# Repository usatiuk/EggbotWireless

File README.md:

# (WIP) EggbotWireless
My attempt at making the ordinary egg-drawing robot a bit special, by ~adding a battery~ and a esp8266 to it.

## Known issues

It's not quite "wireless and portable" yet, for these reasons:

* ~Various battery issues~ (no battery in v2.0!)

* The GCode is generated by inkscape, so you need a computer

## Getting started

### How to build the firmware

Should just work with platformio, but if you're on windows then you need to copy the repo with symlinks 

Also, don't forget to build and upload the LittleFS as well - it contains a simple web interface that allows you to run GCode on the device via Wi-Fi.

If you want to connect to Wi-Fi, then you also should either change the defaults in the ConfigManager.cpp
Or set the configuration via serial:
```
lcp wifiMode client
lcp wifiSSID (your ssid)
lcp wifiPass (your password)
lcw
```
*(lcp stands for "local config put")*

*(lcw stands for "local config write") which saves it to EEPROM*

### How to create GCode

Creating gcode for this thing is quite tricky - you can use the gcodetools Inkscape extension.

The process is supposed to be like this:

1. Open Utils/egg.svg with Inkscape
2. Insert something you want to draw as a child of Layer 1 (the rectangle is the egg boundary)
3. Make it a path
4. Use path to gcode (Also set minimal arc radius in the settings to something big as drawing arcs with g02 is not supported)

You can look at spiral.svg for an example

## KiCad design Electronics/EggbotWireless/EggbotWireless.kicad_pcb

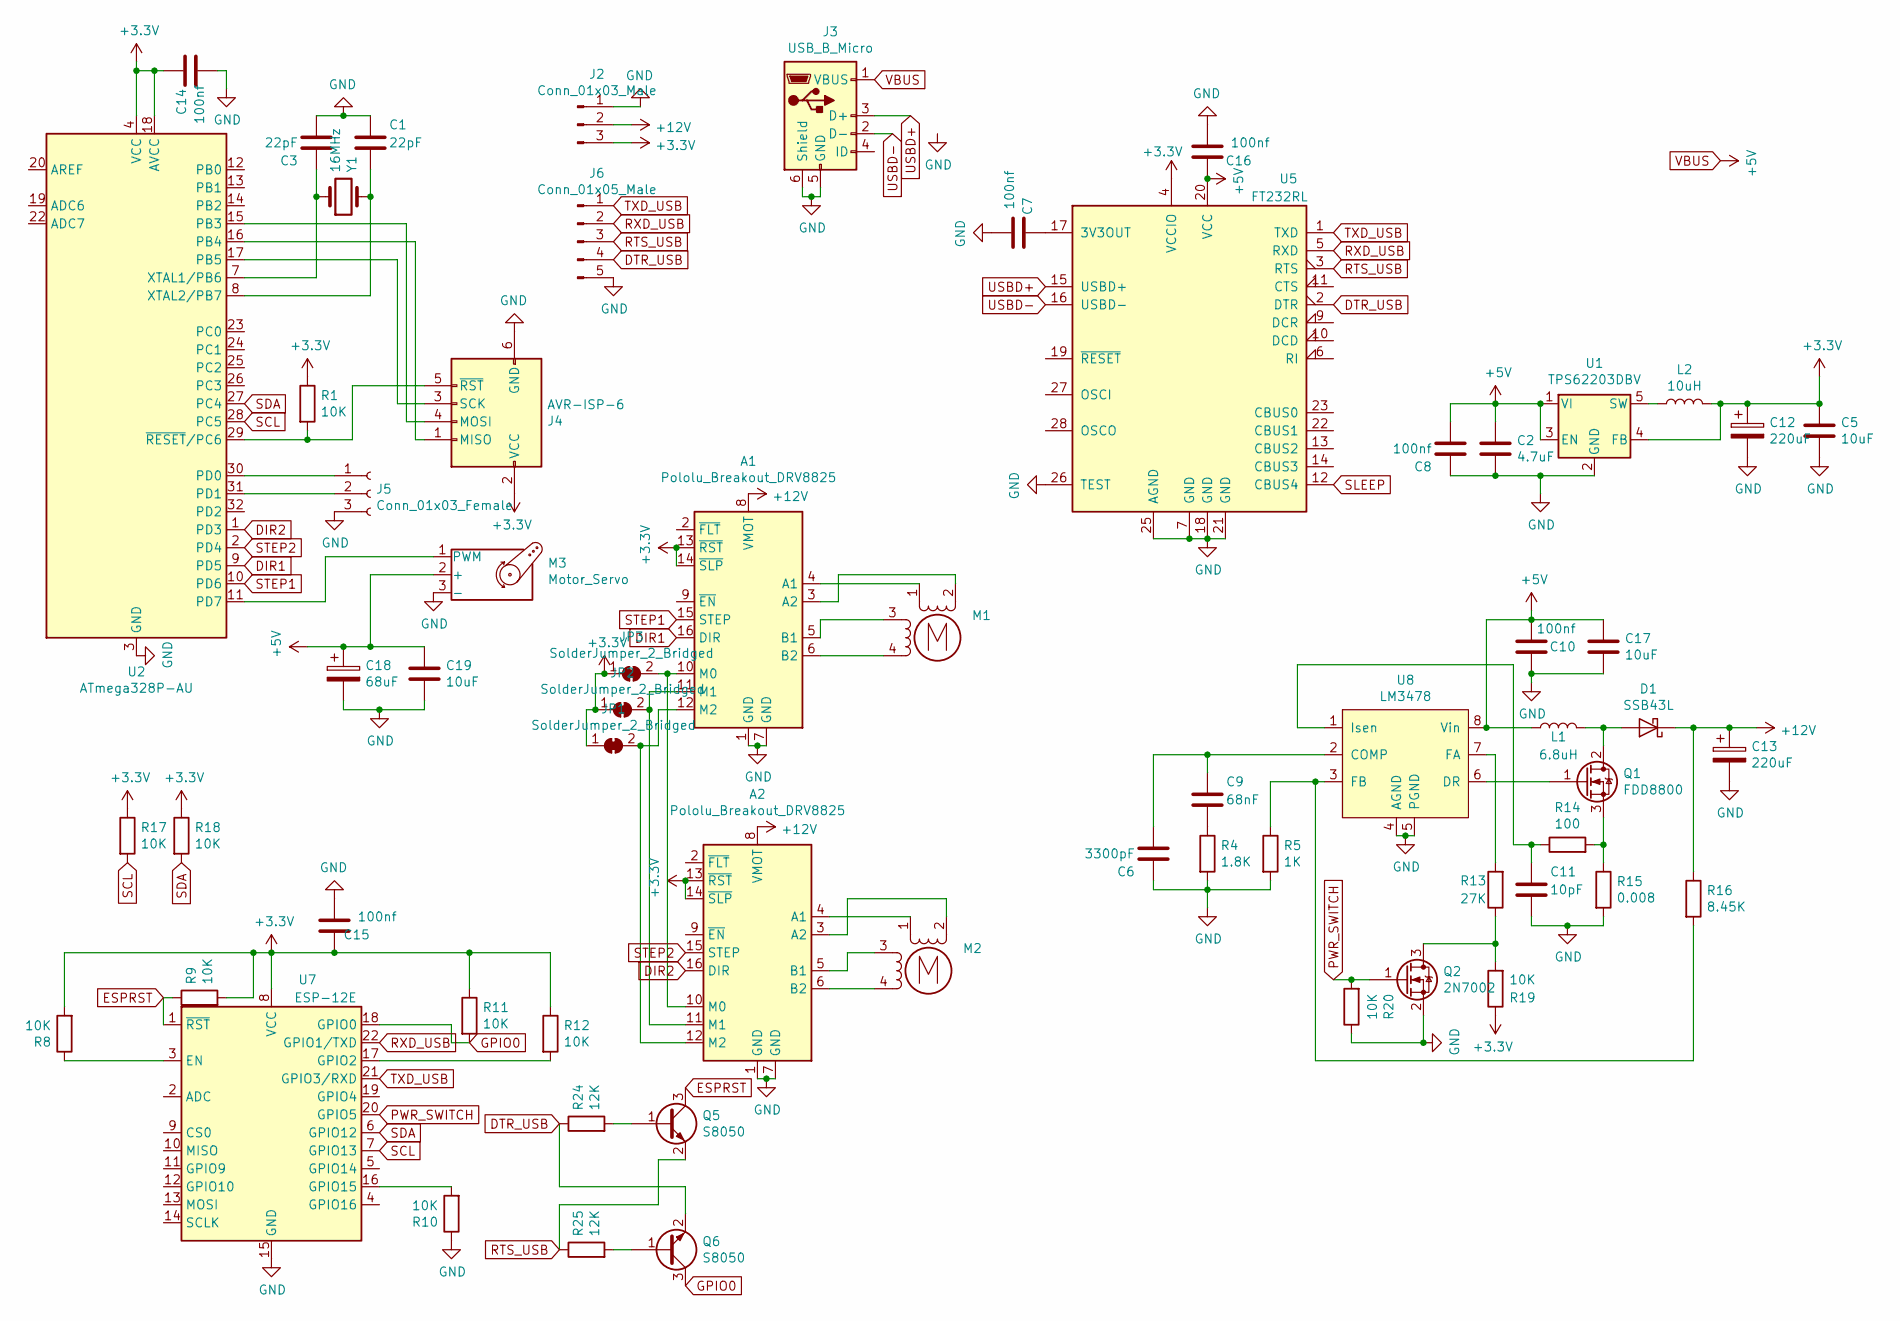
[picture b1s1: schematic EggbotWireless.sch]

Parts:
A1, A2: Pololu_Breakout_DRV8825; Pololu_Breakout-16_15.2x20.3mm
C1, C3: 22pF; C_0805_2012Metric_Pad1.15x1.40mm_HandSolder
C2: 4.7uF; C_0805_2012Metric_Pad1.15x1.40mm_HandSolder
C5, C17: 10uF; C_0805_2012Metric_Pad1.15x1.40mm_HandSolder
C6: 3300pF; C_0805_2012Metric_Pad1.15x1.40mm_HandSolder
C7, C10, C14, C15, C16: 100nf; C_0805_2012Metric_Pad1.15x1.40mm_HandSolder
C8: 100nf; C_0805_2012Metric_Pad1.18x1.45mm_HandSolder
C9: 68nF; C_0805_2012Metric_Pad1.15x1.40mm_HandSolder
C11: 10pF; C_0805_2012Metric_Pad1.15x1.40mm_HandSolder
C12, C13: 220uF; CP_Elec_8x10.5
C18: 68uF; CP_Elec_4x5.8
C19: 10uF; C_0805_2012Metric_Pad1.18x1.45mm_HandSolder
D1: SSB43L; D_SMB_Handsoldering
J2: Conn_01x03_Male; PinHeader_1x03_P2.54mm_Vertical
J3: USB_B_Micro; USB_Micro-B_Molex-105017-0001
J4: AVR-ISP-6; PinHeader_2x03_P2.54mm_Vertical
J5: Conn_01x03_Female; PinHeader_1x03_P2.54mm_Vertical
J6: Conn_01x05_Male; PinHeader_1x05_P2.54mm_Vertical
JP1, JP2, JP3: SolderJumper_2_Bridged; SolderJumper-2_P1.3mm_Bridged_Pad1.0x1.5mm
L1: 6.8uH; L_7.3x7.3_H4.5
L2: 10uH; L_6.3x6.3_H3
M1, M2: PinHeader_1x04_P2.54mm_Vertical
M3: Motor_Servo; PinHeader_1x03_P2.54mm_Vertical
Q1: FDD8800; TO-252-2
Q2: 2N7002; SOT-23
Q5, Q6: S8050; SOT-23
R1, R8, R9, R10, R11, R12, R17, R18, R19, R20: 10K; R_0805_2012Metric_Pad1.15x1.40mm_HandSolder
R4: 1.8K; R_0805_2012Metric_Pad1.15x1.40mm_HandSolder
R5: 1K; R_0805_2012Metric_Pad1.15x1.40mm_HandSolder
R13: 27K; R_0805_2012Metric_Pad1.15x1.40mm_HandSolder
R14: 100; R_0805_2012Metric_Pad1.15x1.40mm_HandSolder
R15: 0.008; R_1206_3216Metric_Pad1.42x1.75mm_HandSolder
R16: 8.45K; R_0805_2012Metric_Pad1.15x1.40mm_HandSolder
R24, R25: 12K; R_0805_2012Metric_Pad1.15x1.40mm_HandSolder
U1: TPS62203DBV; SOT-23-5
U2: ATmega328P-AU; TQFP-32_7x7mm_P0.8mm
U5: FT232RL; SSOP-28_5.3x10.2mm_P0.65mm
U7: ESP-12E
U8: LM3478; VSSOP-8_3.0x3.0mm_P0.65mm
Y1: 16MHz; Crystal_HC49-4H_Vertical

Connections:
+3V3: A1.13 (~RST), A1.14 (~SLP), A2.13 (~RST), A2.14 (~SLP), C5.1, C12.1, C14.2, C15.2, J2.3, J4.2 (VCC), JP1.1 (A), JP2.1 (A), JP3.1 (A), L2.2, R1.1, R8.2, R9.2, R11.1, R12.1, R17.1, R18.1, R19.1, U1.4 (FB), U2.4 (VCC), U2.6 (VCC), U2.18 (AVCC), U5.4 (VCCIO), U7.8 (VCC)
+12V: A1.8 (VMOT), A2.8 (VMOT), C13.1, D1.1 (K), J2.2, R16.1
DIR1: A1.16 (DIR), U2.9 (PD5)
DIR2: A2.16 (DIR), U2.1 (PD3)
DTR_USB: J6.4, Q6.2 (E), R24.1, U5.2 (DTR)
ESPRST: Q5.3 (C), R9.1, U7.1 (~RST)
GND: A1.1 (GND), A1.7 (GND), A2.1 (GND), A2.7 (GND), C1.2, C2.2, C3.1, C5.2, C6.2, C7.1, C8.2, C10.2, C11.1, C12.2, C13.2, C14.1, C15.1, C16.1, C17.2, C18.2, C19.2, J2.1, J3.5 (GND), J3.6 (Shield), J4.6 (GND), J5.3, J6.5, M3.3 (-), Q2.2 (S), R4.2, R5.2, R10.1, R15.2, R20.1, U1.2 (GND), U2.3 (GND), U2.5 (GND), U2.21 (GND), U5.7 (GND), U5.18 (GND), U5.21 (GND), U5.25 (AGND), U5.26 (TEST), U7.15 (GND), U8.4 (AGND), U8.5 (PGND)
GPIO0: Q6.3 (C), R11.2, U7.18 (GPIO0)
unnamed: A1.3 (A2), M1.2 (-)
unnamed: A1.4 (A1), M1.1
unnamed: A1.5 (B1), M1.3
unnamed: A1.6 (B2), M1.4
unnamed: A1.10 (M0), A2.10 (M0), JP3.2 (B)
unnamed: A1.11 (M1), A2.11 (M1), JP2.2 (B)
unnamed: A1.12 (M2), A2.12 (M2), JP1.2 (B)
unnamed: A2.3 (A2), M2.2 (-)
unnamed: A2.4 (A1), M2.1
unnamed: A2.5 (B1), M2.3
unnamed: A2.6 (B2), M2.4
unnamed: C1.1, U2.8 (XTAL2/PB7), Y1.2
unnamed: C3.2, U2.7 (XTAL1/PB6), Y1.1
unnamed: C6.1, C9.2, U8.2 (COMP)
unnamed: C7.2, U5.17 (3V3OUT)
unnamed: C9.1, R4.1
unnamed: C11.2, R14.1, U8.1 (Isen)
unnamed: D1.2 (A), L1.2, Q1.2 (D)
unnamed: J4.1 (MISO), U2.16 (PB4)
unnamed: J4.3 (SCK), U2.17 (PB5)
unnamed: J4.4 (MOSI), U2.15 (PB3)
unnamed: J4.5 (~RST), R1.2, U2.29 (~RESET~/PC6)
unnamed: J5.1, U2.30 (PD0)
unnamed: J5.2, U2.31 (PD1)
unnamed: L2.1, U1.5 (SW)
unnamed: M3.1 (PWM), U2.11 (PD7)
unnamed: Q1.1 (G), U8.6 (DR)
unnamed: Q1.3 (S), R14.2, R15.1
unnamed: Q2.3 (D), R13.1, R19.2
unnamed: Q5.1 (B), R24.2
unnamed: Q6.1 (B), R25.2
unnamed: R8.1, U7.3 (EN)
unnamed: R10.2, U7.16 (GPIO15)
unnamed: R12.2, U7.17 (GPIO2)
unnamed: R13.2, U8.7 (FA)
unnamed: R5.1, R16.2, U8.3 (FB)
PWR_SWITCH: Q2.1 (G), R20.2, U7.20 (GPIO5)
RTS_USB: J6.3, Q5.2 (E), R25.1, U5.3 (RTS)
RXD_USB: J6.2, U5.5 (RXD), U7.22 (GPIO1/TXD)
SCL: R17.2, U2.28 (PC5), U7.7 (GPIO13)
SDA: R18.2, U2.27 (PC4), U7.6 (GPIO12)
STEP1: A1.15 (STEP), U2.10 (PD6)
STEP2: A2.15 (STEP), U2.2 (PD4)
TXD_USB: J6.1, U5.1 (TXD), U7.21 (GPIO3/RXD)
USBD+: J3.3 (D+), U5.15 (USBD+)
USBD-: J3.2 (D-), U5.16 (USBD-)
VBUS: C2.1, C8.1, C10.1, C16.2, C17.1, C18.1, C19.1, J3.1 (VBUS), L1.1, M3.2 (+), U1.1 (VI), U1.3 (EN), U5.20 (VCC), U8.8 (Vin)

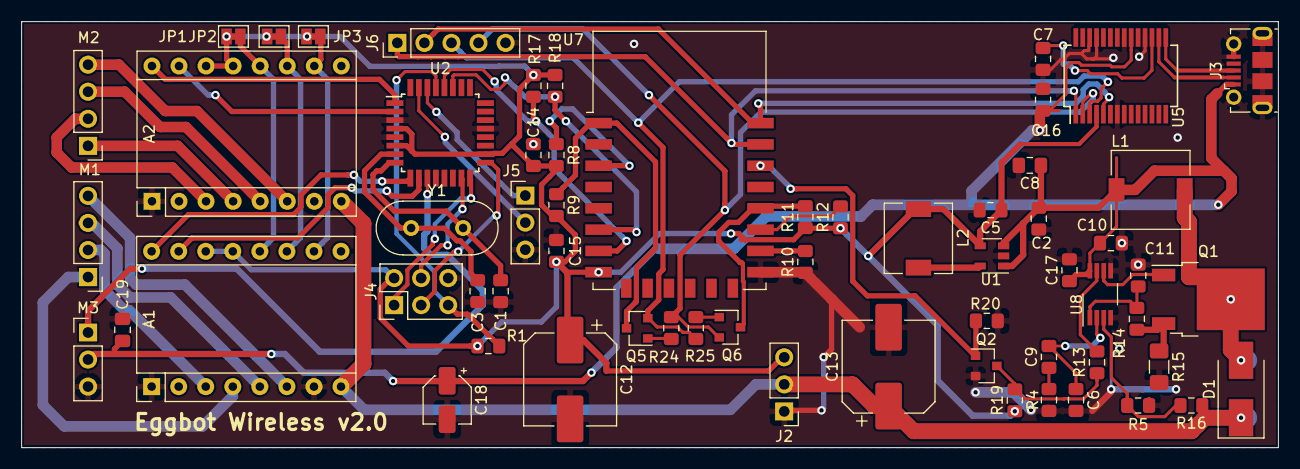
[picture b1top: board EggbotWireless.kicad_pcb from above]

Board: 2 copper layers, 118.0 x 40.0 mm, 62 parts (0 on the bottom side), 55 nets.

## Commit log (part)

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2019-05-03 init
2019-05-03 add front/back plates
2019-05-03 add pen mount plate
2019-05-03 add stepper egg holder
2019-05-03 add bearing egg holder
2019-05-03 design prototype 1
2019-05-03 remove unnecessaray hole
2019-05-03 add a ball bearing model
2019-05-04 some tweaks
2019-05-04 some more tweaks
2019-05-04 spring loaded egg
2019-05-04 tweaks to the marker mount
2019-05-04 even more tweaks
2019-05-05 tolerance adjustments
2019-05-06 prototype v0.2
2019-05-08 Hello, PlatformIO!
2019-05-09 timer-driven stepper driver
2019-05-09 stepper backlash compensation
2019-05-09 keep track of stepper's position
2019-05-09 basic gcode parsing
2019-05-09 adjust tolerance
2019-05-09 better pen control
2019-05-09 more tolerance adjustments
2019-05-09 support longer gcode lines
2019-05-09 use floats to parse gcode
2019-05-09 proper linear interpolation
2019-05-09 change servo positions
2019-05-10 more advanced backlash compensation
2019-05-10 support for G00 command
2019-05-10 set 160mhz cpu speed
2019-05-10 fix backlash comp
2019-05-10 disable backlash compensation for servo stepper
2019-05-10 simple tool to send gcode
2019-05-10 make y axis use nema 17 stepper
2019-05-10 correct y stepper shaft
2019-05-10 make x axis use nema17 stepper
2019-05-10 make pen holder thicker
2019-05-16 use atmega32 to control stepper motors
2019-05-18 fix pen servo
2019-05-24 start working on schematic
2019-05-24 pcb prototype v0.1 (no steppers yet)
2019-05-24 thicker battery traces
2019-05-24 change stepper driver to drv8825
2019-05-24 minor board tweaks
2019-05-24 add steppers to the board
2019-05-24 add branding
2019-05-25 fix servo sizing
2019-05-25 fix case
2019-05-25 fix case (again)
2019-05-25 add switch to the board
2019-05-25 add a hole for servo wire
2019-05-25 change atmega16 to atmega32 in schematic
2019-05-26 fix screw hole in stepper servo holder
2019-05-26 fix lower servo screw hole
2019-05-26 use m4 screw for pen holder
2019-05-26 place egg higher
2019-05-26 better pcb mount
2019-05-26 proper 12v shutdown circuit
2019-05-26 fix shutdown circuit
2019-05-26 tighter fit for StepperEgg
2019-05-27 add screw hole to StepperEgg
2019-05-27 better fit for StepperEgg
2019-05-28 pcb proto v1
2019-05-28 make it work with drv8825 driver
2019-05-28 some adjustments to stepper control mechanism
2019-05-29 remove moving flag
2019-05-29 eggs seem to be bigger than i thought
2019-05-29 fix an annoying bug
2019-05-29 move calling adjustRPM out of the loop
2019-05-29 a better pen holder
2019-06-19 use ft232rl for usb ic, better power handling
2019-06-19 add uart pin header for esp12
2019-06-20 pcb v1.1 proto
2019-06-20 use nodemcu reset circuit
2019-07-10 fit code to the new board
2019-07-10 fix issue with ft232rl being powered with rx/tx board v1.1b
2019-07-10 board v1.2 use p-mosfet for charge enable/disable use sleep instead of pwren connect battery to esp adc via voltage divider
2019-07-11 clean up pcb a little bit
2019-07-13 better mosfets heat dissipation v1.2b
2019-07-15 fix some power issues
2019-07-15 better crystal routing
2019-07-15 fix timer interrupt issues
2019-07-15 disable 12v after 20s of inactivity
2019-07-16 board v1.3
2019-07-17 make inductor 6.8uH
2019-07-22 move command execution out of main.cpp
2019-07-22 cleanup power handling code
2019-07-22 clean up loop()
2019-07-22 add a comment
2019-07-23 rename updateExecution() to steppersRoutine()
2019-07-23 streamline GCodeParser
2019-07-23 less magic numbers
2019-07-24 more efficient args parsing
2019-07-25 config manager thingy, local commands use std::string as much as possible
2019-07-25 store config in "eeprom"
2019-07-26 command queue, default settings
2019-07-26 basic wifi thingy
2019-07-29 status now always reports position
2019-07-30 feature to set feedrate
2019-07-31 a basic web server
2019-08-01 make a QueueManager
2019-08-01 putCommand api
2019-08-02 setup a web app
2019-08-02 webapi returns an actual status message
2019-08-03 basic gcode sender thing
2019-08-05 gcode parser thing
2019-08-05 a simple gcode visualiser
2019-08-05 await for setState
2019-08-05 v1.3f some changes to the schematic
2019-08-05 fix one weird bug
2019-08-05 pen engaged smaller angle
2019-08-06 some minor tweaks
2019-08-06 fix servo glitches on low voltage
2019-08-06 why did i even think of THAT?
2019-08-06 serve the webapp from esp8266
2019-08-07 better web app layout
2019-09-07 return actual battery voltage in status
2019-09-14 fix case pcb stand size
2019-10-23 specify servo lib as a dependency
2019-12-29 Bump handlebars from 4.1.2 to 4.5.3 in /App
    Bumps [handlebars](https://github.com/wycats/handlebars.js) from 4.1.2 to 4.5.3.
    - [Release notes](https://github.com/wycats/handlebars.js/releases)
    - [Changelog](https://github.com/wycats/handlebars.js/blob/master/release-notes.md)
    - [Commits](https://github.com/wycats/handlebars.js/compare/v4.1.2...v4.5.3)
2020-01-03 add 5v boost schematic
2020-01-03 v1.4 beta board (added a 5v boost converter to the board)
2020-01-26 more detailed egg holder design
2020-01-26 rubber band tensioner for pen holder
2020-01-28 change 5vboost inductor to smaller
2020-02-02 make penHolder hinge gap smaller again (because otherwise servo horn could break it)
2020-03-17 add a BOM
2020-03-18 5vboost working
2020-03-19 slow down i2c because it didn't work at 1MHz ATMega
2020-03-19 use MiniCore for ATMega
2020-03-19 remove pen hotfix now with proper power it should work
2020-03-19 [AVR] initialize pen before everything else
2020-03-19 [ESP] WiFi.reconnect() when connecting to the ap
2020-03-19 [App] update deps
2020-03-19 [App] use current window's hostname for api calls
2020-03-19 [Board] fix some issues 1. change 5vboost output capacitor to 68 uF 2. change ATMega crystal to 12MHz
2020-03-19 add spiral example gcode
2020-03-19 add ignoreRpm option, because gcodetools default is 400
2020-03-19 [AVR] smooth servo
2020-03-19 [AVR] use a watchdog to keep this thing from freezing
2020-03-19 fix servo not disengaging
2020-03-20 [ESP] increase power timeout
2020-03-20 more precise movements
2020-05-08 Create LICENSE
2020-06-08 add some documentation
2020-07-05 change battery mosfet to FDS6898AZ Servo motor kind of works now, but not enough power for wi-fi, and it resets sometimes: 5v boost redesign needed - I didn't expect that much power draw from a servo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
2020-07-06 add 5v booster bypass for servo
2020-07-06 add all the new components to the board
2020-07-06 TPS61023 - based 5v booster
2020-07-06 rename the board to v1.5
2020-07-07 use Servo library id instead of name because there are multiple "Servo" libraries
2020-11-28 change crystal to 16MHz
2020-12-03 remove all remnants of battery circuitry. Hopefully works
2020-12-06 filet pen holder because otherwise the layers can split
2020-12-06 [ESP] use littlefs
2020-12-06 update web app and auto build
2020-12-07 3v3StepDown module
2020-12-07 fix 12vboost transistor typo
2020-12-07 3v3 boost in dip body
2020-12-13 do not commit built web app files
2020-12-14 12vBoost module
2020-12-22 Bump node-notifier from 8.0.0 to 8.0.1 in /App
    Bumps [node-notifier](https://github.com/mikaelbr/node-notifier) from 8.0.0 to 8.0.1.
    - [Release notes](https://github.com/mikaelbr/node-notifier/releases)
    - [Changelog](https://github.com/mikaelbr/node-notifier/blob/v8.0.1/CHANGELOG.md)
    - [Commits](https://github.com/mikaelbr/node-notifier/compare/v8.0.0...v8.0.1)
2020-12-23 config EggbotWireless with 12Boost module
2020-12-26 fix esp build
2021-03-09 Bump elliptic from 6.5.3 to 6.5.4 in /App
    Bumps [elliptic](https://github.com/indutny/elliptic) from 6.5.3 to 6.5.4.
    - [Release notes](https://github.com/indutny/elliptic/releases)
    - [Commits](https://github.com/indutny/elliptic/compare/v6.5.3...v6.5.4)
2021-05-09 remove power switch (no need without battery), v2.0!!!
2021-05-10 fix solder mask clearance
2021-05-10 Bump lodash from 4.17.20 to 4.17.21 in /App
    Bumps [lodash](https://github.com/lodash/lodash) from 4.17.20 to 4.17.21.
    - [Release notes](https://github.com/lodash/lodash/releases)
    - [Commits](https://github.com/lodash/lodash/compare/4.17.20...4.17.21)
2021-05-10 fix 12v boost transistor part name typo
2021-05-12 Bump postcss from 8.1.14 to 8.2.10 in /App
    Bumps [postcss](https://github.com/postcss/postcss) from 8.1.14 to 8.2.10.
    - [Release notes](https://github.com/postcss/postcss/releases)
    - [Changelog](https://github.com/postcss/postcss/blob/main/CHANGELOG.md)
    - [Commits](https://github.com/postcss/postcss/compare/8.1.14...8.2.10)
2021-05-12 Bump hosted-git-info from 2.8.8 to 2.8.9 in /App
    Bumps [hosted-git-info](https://github.com/npm/hosted-git-info) from 2.8.8 to 2.8.9.
    - [Release notes](https://github.com/npm/hosted-git-info/releases)
    - [Changelog](https://github.com/npm/hosted-git-info/blob/v2.8.9/CHANGELOG.md)
    - [Commits](https://github.com/npm/hosted-git-info/compare/v2.8.8...v2.8.9)
2021-06-20 Bump browserslist from 4.15.0 to 4.16.6 in /App
    Bumps [browserslist](https://github.com/browserslist/browserslist) from 4.15.0 to 4.16.6.
    - [Release notes](https://github.com/browserslist/browserslist/releases)
    - [Changelog](https://github.com/browserslist/browserslist/blob/main/CHANGELOG.md)
    - [Commits](https://github.com/browserslist/browserslist/compare/4.15.0...4.16.6)
2021-06-29 update BOM
2021-06-29 fix esp platform version
2021-06-29 fix avr uploading
2021-06-29 do not overload the esp with status requests
2021-06-29 change WDT to 500ms
2021-06-29 fix upload not working
2021-06-29 fix wrong delay computations, some debug output
2021-07-17 optimize images
2025-06-24 Bump pbkdf2 from 3.1.1 to 3.1.3 in /App
    Bumps [pbkdf2](https://github.com/crypto-browserify/pbkdf2) from 3.1.1 to 3.1.3.
    - [Changelog](https://github.com/browserify/pbkdf2/blob/master/CHANGELOG.md)
    - [Commits](https://github.com/crypto-browserify/pbkdf2/compare/v3.1.1...v3.1.3)
    ---
    updated-dependencies:
    - dependency-name: pbkdf2
2025-08-22 Bump sha.js from 2.4.11 to 2.4.12 in /App
    Bumps [sha.js](https://github.com/crypto-browserify/sha.js) from 2.4.11 to 2.4.12.
    - [Changelog](https://github.com/browserify/sha.js/blob/master/CHANGELOG.md)
    - [Commits](https://github.com/crypto-browserify/sha.js/compare/v2.4.11...v2.4.12)
    ---
    updated-dependencies:
    - dependency-name: sha.js
2025-09-30 Bump lodash-es from 4.17.15 to 4.17.21 in /App
    Bumps [lodash-es](https://github.com/lodash/lodash) from 4.17.15 to 4.17.21.
    - [Release notes](https://github.com/lodash/lodash/releases)
    - [Commits](https://github.com/lodash/lodash/compare/4.17.15...4.17.21)
    ---
    updated-dependencies:
    - dependency-name: lodash-es
2025-11-18 Bump js-yaml from 3.14.0 to 3.14.2 in /App
    Bumps [js-yaml](https://github.com/nodeca/js-yaml) from 3.14.0 to 3.14.2.
    - [Changelog](https://github.com/nodeca/js-yaml/blob/master/CHANGELOG.md)
    - [Commits](https://github.com/nodeca/js-yaml/compare/3.14.0...3.14.2)
    ---
    updated-dependencies:
    - dependency-name: js-yaml
2026-01-22 Bump lodash from 4.17.21 to 4.17.23 in /App
    Bumps [lodash](https://github.com/lodash/lodash) from 4.17.21 to 4.17.23.
    - [Release notes](https://github.com/lodash/lodash/releases)
    - [Commits](https://github.com/lodash/lodash/compare/4.17.21...4.17.23)
    ---
    updated-dependencies:
    - dependency-name: lodash
2026-01-22 Bump lodash-es from 4.17.15 to 4.17.23 in /App
    Bumps [lodash-es](https://github.com/lodash/lodash) from 4.17.15 to 4.17.23.
    - [Release notes](https://github.com/lodash/lodash/releases)
    - [Commits](https://github.com/lodash/lodash/compare/4.17.15...4.17.23)
    ---
    updated-dependencies:
    - dependency-name: lodash-es
